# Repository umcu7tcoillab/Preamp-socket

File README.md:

# Preamp socket for WMA7RA-R5 / WMA1R0C (WanTcom)

## About us
This design has been made by the coil-lab of the High Field MRI Group of the UMC Utrecht in the Netherlands, where we make hardware to support our researchers. We are part of a research group which means we feel the need to open up some of our designs to whomever can make use of it, to further the research of MRI applications.

## The design
This project contains a socket for the WMA7RA-R5, WMA1R0C and similar preamps made by WanTcom. This socket makes it possible to quickly change the preamp in case of breakage, as well as easier repair than when they are soldered on larger boards.

There are two different designs. One for the WMA7RA-R5 type (1.5/3/7/9.5T), and one for the WMA1R0C type (1T).

The design and subsequent drawing has been done in Kicad 5.1.5.

## Download
Gerber and BOM production files for the latest _field tested_ version of the PCB can be found in the 'Releases' page, or by following [this link](https://github.com/umcu7tcoillab/Preamp-socket/releases/latest). 
You can also make your own production files by downloading the Kicad project and generating them, but these are not guaranteed to have been field tested.

## Images
**3D Image Preampboard 1.5/3/7/9.5T**

**3D Image Preampboard 1T**

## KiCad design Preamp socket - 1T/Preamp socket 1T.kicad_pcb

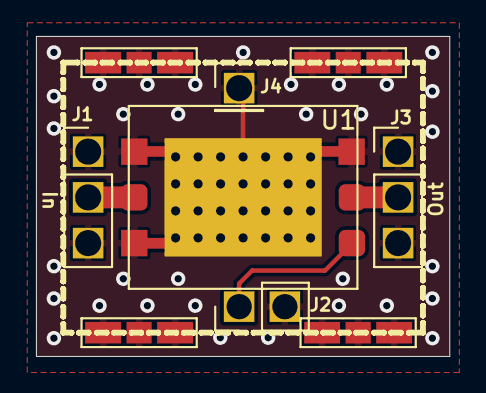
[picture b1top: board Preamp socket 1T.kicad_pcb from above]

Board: 2 copper layers, 23.0 x 17.8 mm, 11 parts (1 on the bottom side), 4 nets.

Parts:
G1: LOGO; UMC_logo_small
J1: In; Preci-dip_PinHeader_1x03_rect
J2: VCC; Preci-dip_PinHeader_1x02_rect
J3: Out; Preci-dip_PinHeader_1x03_rect
J4: GND; Preci-dip_PinHeader_1x01_rect
S2, S4, S5, S6: shield_clip; S0971-46R-shield_clip
Sh1: RF_Shield_One_Piece; Shield_15mm_20mm
U1: Preamp; Preamp_WMA1R0C

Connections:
GND: J1.1, J1.3, J2.2, J3.1, J3.3, J4.1, S2.1, S4.1, S5.1, S6.1, U1.4
unnamed: J1.2, U1.1
unnamed: J2.1, U1.2
unnamed: J3.2, U1.3

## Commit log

2020-02-11 Changed: adjusted for shield clips
2020-02-11 Changed: better outlining of parts
2020-02-11 Chnaged: via locations
2020-02-25 Added: 1T preamp socket. 3D renders.
2020-03-05 Updated 3D settings
2020-03-05 Updated LICENSE
2020-03-12 Changed: header hole size, header to preci-dip header
2020-03-19 Changed: headers to 1.4mm for preci-dip
2020-03-19 removed: local library reference
2020-03-19 Update 3D images
2021-11-24 Rescue libraries, small changes.V0.3
2021-11-24 Part of previous commit..
2021-11-24 Correct board thickness and solder mask clearance
2021-11-24 Updated to v1.0
2021-11-24 Updated version date
